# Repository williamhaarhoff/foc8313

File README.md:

# foc8313
This board was inspired by [Foc-Ctrl-Lite](https://github.com/peng-zhihui/Ctrl-FOC-Lite). FOC8313 is a highly compact, feature rich, daisy-chainable,  field oriented control board based around the DRV8313 3 phase half bridge driver. This board is highly configurable and upgradeable, and includes all the manufacturing files required start producing controllers for $\approx$ $20/board
|Front|Back|
|--| --|
| | |

## Features:
 - Highly compact 35x35mm outline
 - 29x29 square M3 hole pattern
 - 12V to 35V operating range
 - 3.5A max per phase current
 - Onboard STM32F103CBTx microcontroller
 - Based on the DRV8313 3 phase half bridge driver
 - 2 x INA240A2D high side current sense amplifiers
 - 1 x AS5047D back mounted hall effect encoder
 - EEPROM to store configurations / calibrations etc. 
 - Daisy chainable power and CAN
 - Programmable with USB-DFU or StLink - 6 pin tag connect
 - Auxilliary encoder/Timer port with 5V and GND
 - Auxilliary SPI/GPIO and I2C/UART port with 5V and GND
 - Easily upgradable for isolated CAN (3 wire)
 - Extremely compact isolated CAN
 - JLC manufacturing files included
 - Cost optimised for PCBA with JLCPCB (as few extended components as possible)
 - Most basic variant costs $\approx$ $20 per board (for 10 PCBs at JLCPCB)
 - Predominantly single sided design allows for cost effective single sided PCBA, easy hot plating for rework, easy configuration with jumpers

| Top | In1 |
|--| --|
|||
|In2 | Bottom|
|||

# PCBA - Cost Scaling:
| Version | Colour | Finish | Assembly      | Quantity | Unit price | Extended Price |
| -----   | ----   | ------ | -----         | -----    | ----       | ------         |
| v1.0    | Black  | Enig   | Standard T&B  | 15       |$30.8       | $462.57        |
| v1.0    | Black  | Enig   | Standard Top  | 15       |$24.3       | $364.22        |
| v1.0    | Black  | HASL   | Standard Top  | 10       |$24.75      | $247.51        |
| v1.0    | Black  | Enig   | Standard T&B  | 100      |$16.78      | $1678.39       |
| v1.0    | Green  | HASL   | Economic Top  | 2        |$53.45      | $106.89        |
| v1.0    | Green  | HASL   | Economic Top  | 5        |$30.28      | $151.40        |
| v1.0    | Green  | HASL   | Economic Top  | 10       |$20.48      | $204.81        |
| v1.0    | Green  | HASL   | Economic Top  | 15       |$19.2       | $288.48        |
| v1.0    | Green  | HASL   | Economic Top  | 30       |$15.6       | $468.48        |
| v1.0    | Green  | HASL   | Standard Top  | 100      |$12.98      | $1297.77       |
| v1.0    | Black  | Enig   | No ICs Top    | 10       |$15.9 +     | $159.37        |
| v1.0    | Black  | Enig   | No ICs Top    | 15       |$12.9 +     | $193.44        |

# ICs:
15x @LCSC: 215.22 -> 14.33
10x @LCSC: 146.71 -> 14.6

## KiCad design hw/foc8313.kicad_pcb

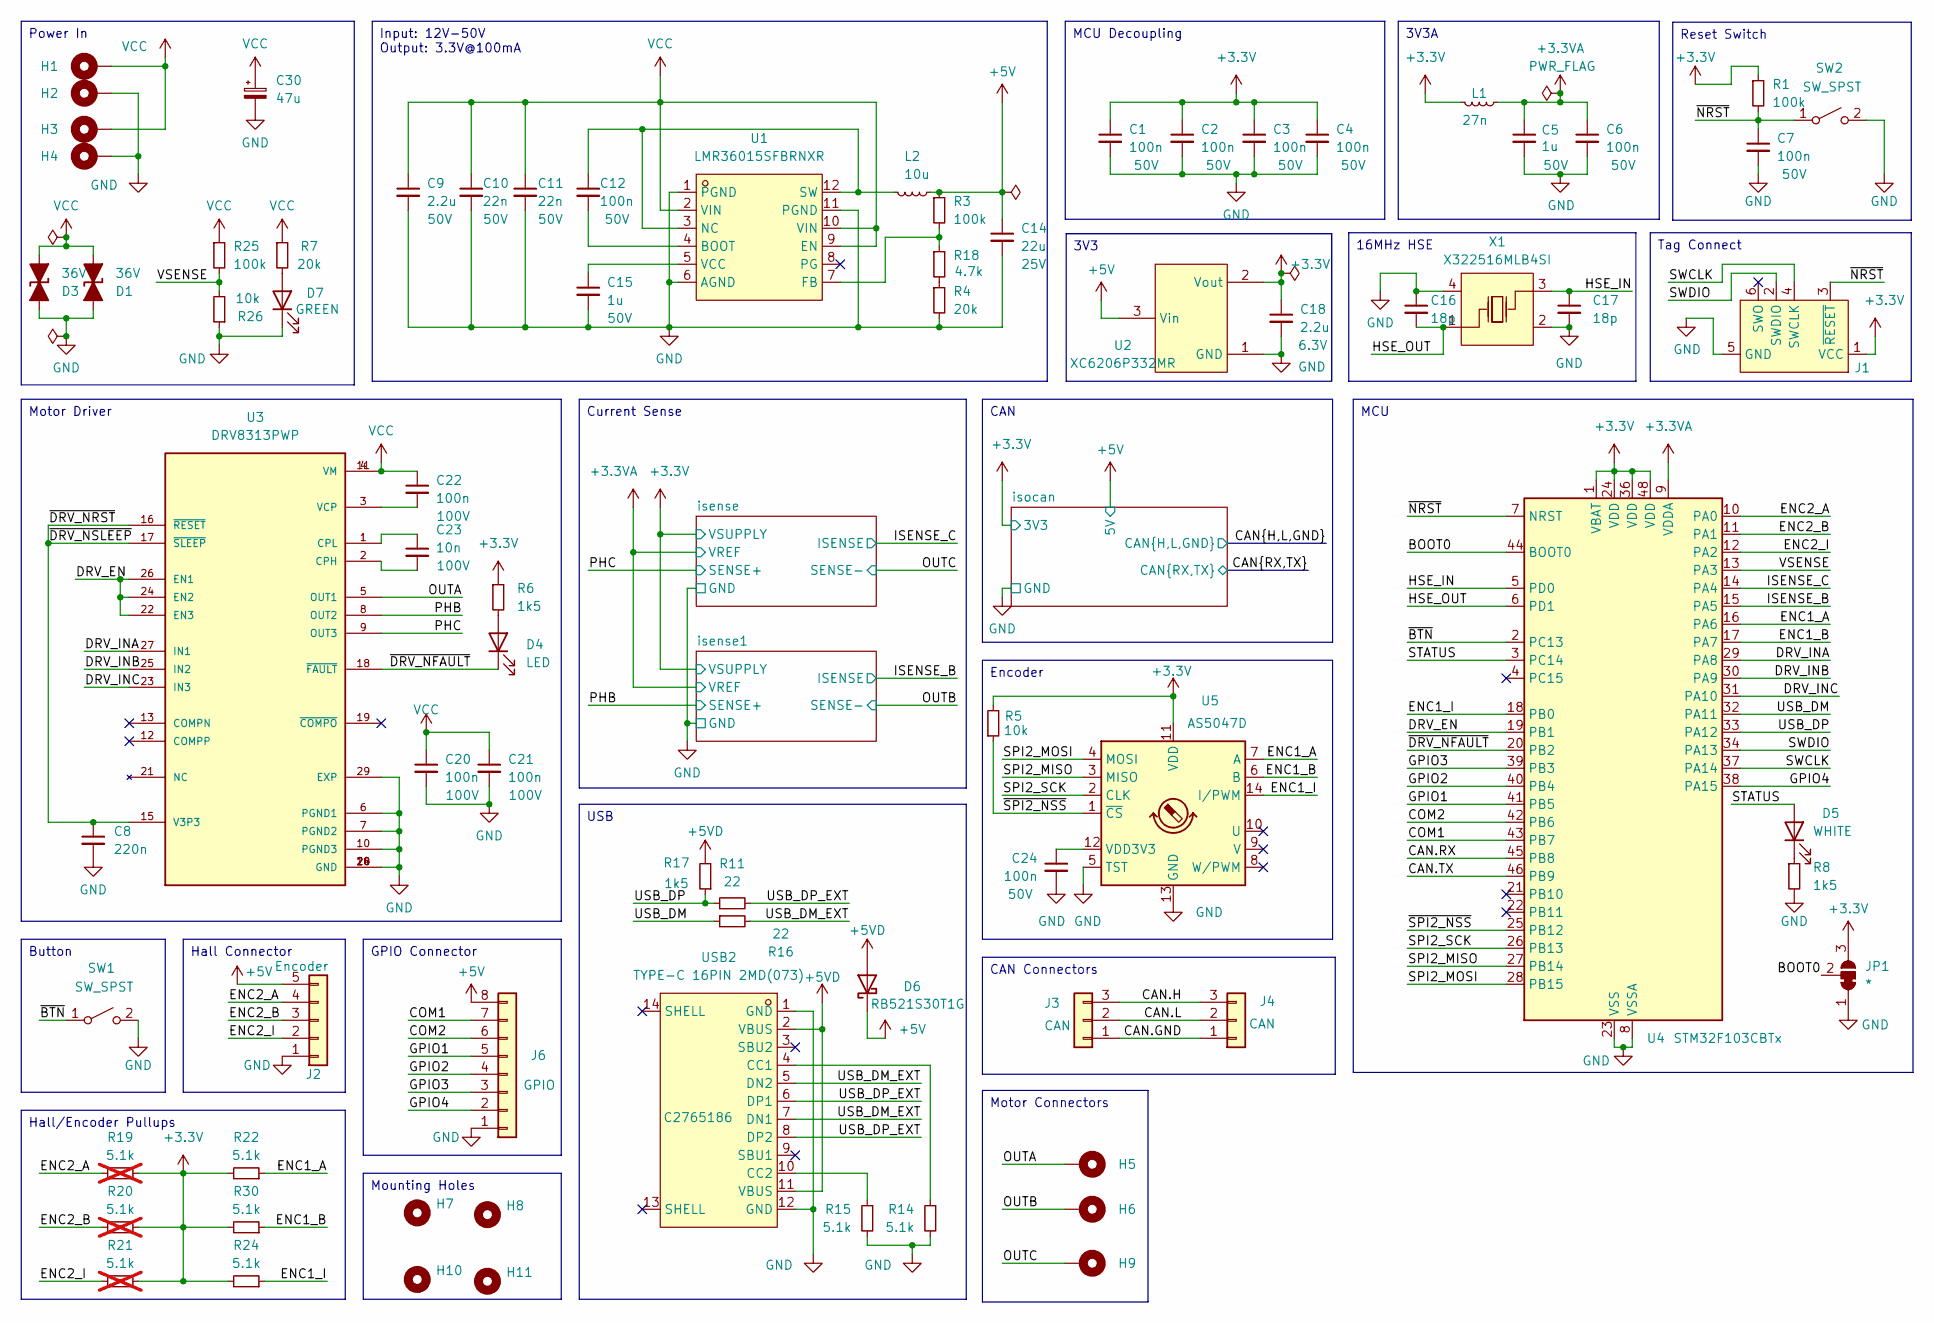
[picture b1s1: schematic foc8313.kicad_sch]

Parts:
C1, C2, C3, C4, C6, C7, C12, C24: 100n; C_0402_1005Metric; Rating 50V; LCSC C307331
C5, C15: 1u; C_0603_1608Metric; Rating 50V; LCSC C15849
C8: 220n; C_0402_1005Metric; LCSC C16772
C9: 2.2u; C_0805_2012Metric; Rating 50V; LCSC C377773
C10, C11: 22n; C_0402_1005Metric; Rating 50V; LCSC C1532
C14: 22u; C_0805_2012Metric; Rating 25V; LCSC C45783
C16, C17: 18p; C_0402_1005Metric; LCSC Part C1549
C18: 2.2u; C_0402_1005Metric; Rating 6.3V; LCSC C12530
C20, C21, C22: 100n; C_0402_1005Metric; Rating 100V; LCSC C307331
C23: 10n; C_0402_1005Metric; Rating 100V; LCSC C15195
C30: 47u; CP_Elec_5x5.7; LCSC C7471868
D1, D3: 36V; D_SOD-323; LCSC C92677
D4: LED; D_0603_1608Metric; LCSC C2286
D5: WHITE; LED_0603_1608Metric; LCSC C2290
D6: RB521S30T1G; D_SOD-523; LCSC C145179
D7: GREEN; LED_0603_1608Metric; LCSC C12624
H1, H2, H3, H4: MountingHole_Pad; 2x4
H5, H6, H9: MountingHole_Pad; 2x3
H7, H8, H10, H11: MountingHole; MountingHole_3.2mm_M3_DIN965_Pad_TopOnly
J1: Tag Connect; Tag-Connect_TC2030-IDC-NL_2x03_P1.27mm_Vertical
J2: Encoder; CONN-SMD_5P-P1.00_MEGASTAR_ZX-SH1.0-5PWT; LCSC Part C7430447
J3, J4: CAN; CONN-SMD_AFC10-S03QCA-00; LCSC Part C2764182
J6: GPIO; CONN-SMD_8P-P1.00_MEGASTAR_ZX-SH1.0-8PWT; LCSC Part C7430450
JP1: *; SolderJumper-3_P1.3mm_Bridged2Bar12_Pad1.0x1.5mm
L1: 27n; L_0603_1608Metric; LCSC C280267
L2: 10u; L_0805_2012Metric; LCSC C285963
R1, R3, R25: 100k; R_0402_1005Metric; LCSC C25741
R4, R7: 20k; R_0402_1005Metric; LCSC C25765
R5, R26: 10k; R_0402_1005Metric; LCSC C25744
R6, R8, R17: 1k5; R_0402_1005Metric; LCSC C25867
R11, R16: 22; R_0402_1005Metric; LCSC C25092
R14, R15, R22, R24, R30: 5.1k; R_0402_1005Metric; LCSC C25905
R18: 4.7k; R_0402_1005Metric; LCSC C25900
R19, R20, R21: 5.1k; R_0402_1005Metric; LCSC C25905; not fitted
SW1, SW2: SW_SPST; SW-TH_PANASONIC_EVPAKE31A; LCSC C569760
U1: LMR36015SFBRNXR; VQFN-12_L3.0-W2.0-P0.65-BL_TI_RNX; LCSC Part C3187929
U2: XC6206P332MR; SOT-23-3_L2.9-W1.6-P1.90-LS2.8-BR; LCSC Part C5446
U3: DRV8313PWP; HTSSOP-28_L9.8-W4.5-P0.65-LS6.6-BL-EP; PARTREV D; LCSC C92482
U4: STM32F103CBTx; LQFP-48_7x7mm_P0.5mm; LCSC C8304
U5: AS5047D; TSSOP-14_4.4x5mm_P0.65mm; LCSC C962063
USB2: TYPE-C 16PIN 2MD(073); USB-C-SMD_TYPE-C-6PIN-2MD-073; LCSC Part C2765186
X1: X322516MLB4SI; OSC-SMD_4P-L3.2-W2.5-BL; LCSC Part C13738

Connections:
+3.3V: C1.1, C2.1, C3.1, C4.1, C18.1, J1.1 (VCC), JP1.3 (B), L1.2, R1.1, R5.2, R6.1, R19.2, R20.2, R21.2, R22.2, R24.2, R30.2, U2.2 (Vout), U4.1 (VBAT), U4.24 (VDD), U4.36 (VDD), U4.48 (VDD), U5.11 (VDD); also elsewhere on the board
+3.3VA: C5.1, C6.1, L1.1, U4.9 (VDDA); also elsewhere on the board
+5V: C14.1, D6.1 (K), J2.5, J6.8, L2.1, R3.1, U2.3 (Vin); also elsewhere on the board
+5VD: D6.2 (A), R17.2, USB2.2 (VBUS), USB2.11 (VBUS)
/BOOT0: JP1.2 (C), U4.44 (BOOT0)
/CAN.GND: J3.1, J4.1; also elsewhere on the board
/CAN.H: J3.3, J4.3; also elsewhere on the board
/CAN.L: J3.2, J4.2; also elsewhere on the board
/CAN.RX: U4.45 (PB8); also elsewhere on the board
/CAN.TX: U4.46 (PB9); also elsewhere on the board
/COM1: J6.7, U4.43 (PB7)
/COM2: J6.6, U4.42 (PB6)
/DRV_EN: U3.22 (EN3), U3.24 (EN2), U3.26 (EN1), U4.19 (PB1)
/DRV_INA: U3.27 (IN1), U4.29 (PA8)
/DRV_INB: U3.25 (IN2), U4.30 (PA9)
/DRV_INC: U3.23 (IN3), U4.31 (PA10)
/ENC1_A: R22.1, U4.16 (PA6), U5.7 (A)
/ENC1_B: R30.1, U4.17 (PA7), U5.6 (B)
/ENC1_I: R24.1, U4.18 (PB0), U5.14 (I/PWM)
/ENC2_A: J2.4, R19.1, U4.10 (PA0)
/ENC2_B: J2.3, R20.1, U4.11 (PA1)
/ENC2_I: J2.2, R21.1, U4.12 (PA2)
/GPIO1: J6.5, U4.41 (PB5)
/GPIO2: J6.4, U4.40 (PB4)
/GPIO3: J6.3, U4.39 (PB3)
/GPIO4: J6.2, U4.38 (PA15)
/HSE_IN: C17.1, U4.5 (PD0), X1.3
/HSE_OUT: C16.2, U4.6 (PD1), X1.1
/ISENSE_B: U4.15 (PA5); also elsewhere on the board
/ISENSE_C: U4.14 (PA4); also elsewhere on the board
/OUTA: H5.1, U3.5 (OUT1)
/OUTB: H6.1; also elsewhere on the board
/OUTC: H9.1; also elsewhere on the board
/PHB: U3.8 (OUT2); also elsewhere on the board
/PHC: U3.9 (OUT3); also elsewhere on the board
/SPI2_MISO: U4.27 (PB14), U5.3 (MISO)
/SPI2_MOSI: U4.28 (PB15), U5.4 (MOSI)
/SPI2_SCK: U4.26 (PB13), U5.2 (CLK)
/STATUS: D5.2 (A), U4.3 (PC14)
/SWCLK: J1.4 (SWCLK), U4.37 (PA14)
/SWDIO: J1.2 (SWDIO), U4.34 (PA13)
/USB_DM: R16.1, U4.32 (PA11)
/USB_DM_EXT: R16.2, USB2.5 (DN2), USB2.7 (DN1)
/USB_DP: R11.1, R17.1, U4.33 (PA12)
/USB_DP_EXT: R11.2, USB2.6 (DP1), USB2.8 (DP2)
/VSENSE: R25.2, R26.2, U4.13 (PA3)
/~BTN: SW1.1 (A), U4.2 (PC13)
/~DRV_NFAULT: D4.1 (K), U3.18 (~FAULT), U4.20 (PB2)
/~DRV_NRST: C8.1, U3.15 (V3P3), U3.16 (~RESET), U3.17 (~SLEEP)
/~NRST: C7.1, J1.3 (~RESET), R1.2, SW2.1 (A), U4.7 (NRST)
/~SPI2_NSS: R5.1, U4.25 (PB12), U5.1 (~CS)
GND: C1.2, C2.2, C3.2, C4.2, C5.2, C6.2, C7.2, C8.2, C9.2, C10.2, C11.2, C14.2, C15.2, C16.1, C17.2, C18.2, C20.2, C21.2, C24.2, C30.2, D1.2 (A2), D3.2 (A2), D7.1 (K), H2.1, H4.1, J1.5 (GND), J2.1, J6.1, JP1.1 (A), R4.2, R8.2, R14.2, R15.2, R26.1, SW1.2 (B), SW2.2 (B), U1.1 (PGND), U1.6 (AGND), U1.11 (PGND), U2.1 (GND), U3.6 (PGND1), U3.7 (PGND2), U3.10 (PGND3), U3.14 (GND), U3.20 (GND), U3.28 (GND), U3.29 (EXP), U4.8 (VSSA), U4.23 (VSS), U4.35 (VSS), U4.47 (VSS), U5.5 (TST), U5.13 (GND), USB2.1 (GND), USB2.12 (GND), X1.2, X1.4; also elsewhere on the board
unnamed: D4.2 (A), R6.2
unnamed: D5.1 (K), R8.1
unnamed: D7.2 (A), R7.2
unnamed: R4.1, R18.2
unnamed: C12.2, U1.4 (BOOT)
unnamed: R3.2, R18.1, U1.7 (FB)
unnamed: C12.1, L2.2, U1.3 (NC), U1.12 (SW)
unnamed: C15.1, U1.5 (VCC)
unnamed: C23.2, U3.2 (CPH)
unnamed: C23.1, U3.1 (CPL)
unnamed: C22.2, U3.3 (VCP)
unnamed: C24.1, U5.12 (VDD3V3)
unnamed: R14.1, USB2.4 (CC1)
unnamed: R15.1, USB2.10 (CC2)
VCC: C9.1, C10.1, C11.1, C20.1, C21.1, C22.1, C30.1, D1.1 (A1), D3.1 (A1), H1.1, H3.1, R7.1, R25.1, U1.2 (VIN), U1.9 (EN), U1.10 (VIN), U3.4 (VM), U3.11 (VM)

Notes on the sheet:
Motor Connectors
Mounting Holes
MCU
CAN Connectors
GPIO Connector
Reset Switch
3V3A
16MHz HSE
3V3
MCU Decoupling
CAN
Hall/Encoder Pullups
Hall Connector
Power In
Encoder
Tag Connect
Current Sense
Button
Motor Driver
USB
Input: 12V-50V Output: 3.3V@100mA

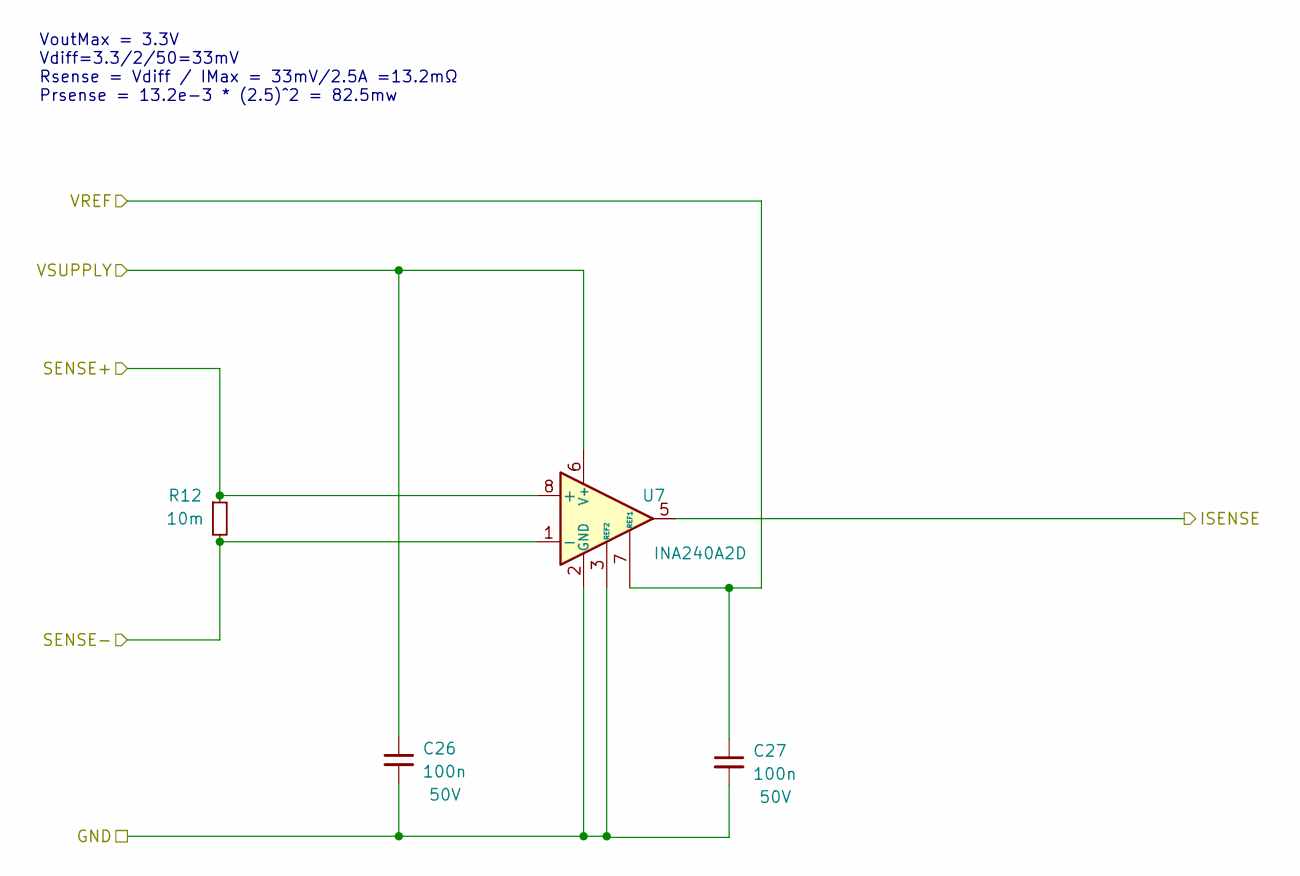
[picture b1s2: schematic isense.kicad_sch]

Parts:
C26, C27: 100n; C_0402_1005Metric; Rating 50V; LCSC C307331
R12: 10m; R_0805_2012Metric; LCSC C601083
U7: INA240A2D; SOIC-8_3.9x4.9mm_P1.27mm; LCSC C2060768

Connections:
+3.3V: C26.1, U7.6 (V+); also elsewhere on the board
+3.3VA: C27.1, U7.7 (REF1); also elsewhere on the board
/ISENSE_C: U7.5; also elsewhere on the board
/OUTC: R12.2, U7.1 (-); also elsewhere on the board
/PHC: R12.1, U7.8 (+); also elsewhere on the board
GND: C26.2, C27.2, U7.2 (GND), U7.3 (REF2), U7.4 (GND); also elsewhere on the board

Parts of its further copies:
C28, C29: 100n; C_0402_1005Metric; Rating 50V; LCSC C307331
R13: 10m; R_0805_2012Metric; LCSC C601083
U8: INA240A2D; SOIC-8_3.9x4.9mm_P1.27mm; LCSC C2060768

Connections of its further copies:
+3.3V: C28.1, U8.6 (V+); also elsewhere on the board
+3.3VA: C29.1, U8.7 (REF1); also elsewhere on the board
/ISENSE_B: U8.5; also elsewhere on the board
/OUTB: R13.2, U8.1 (-); also elsewhere on the board
/PHB: R13.1, U8.8 (+); also elsewhere on the board
GND: C28.2, C29.2, U8.2 (GND), U8.3 (REF2), U8.4 (GND); also elsewhere on the board

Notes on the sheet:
VoutMax = 3.3V Vdiff=3.3/2/50=33mV Rsense = Vdiff / IMax = 33mV/2.5A =13.2mΩ Prsense = 13.2e-3 * (2.5)^2 = 82.5mw

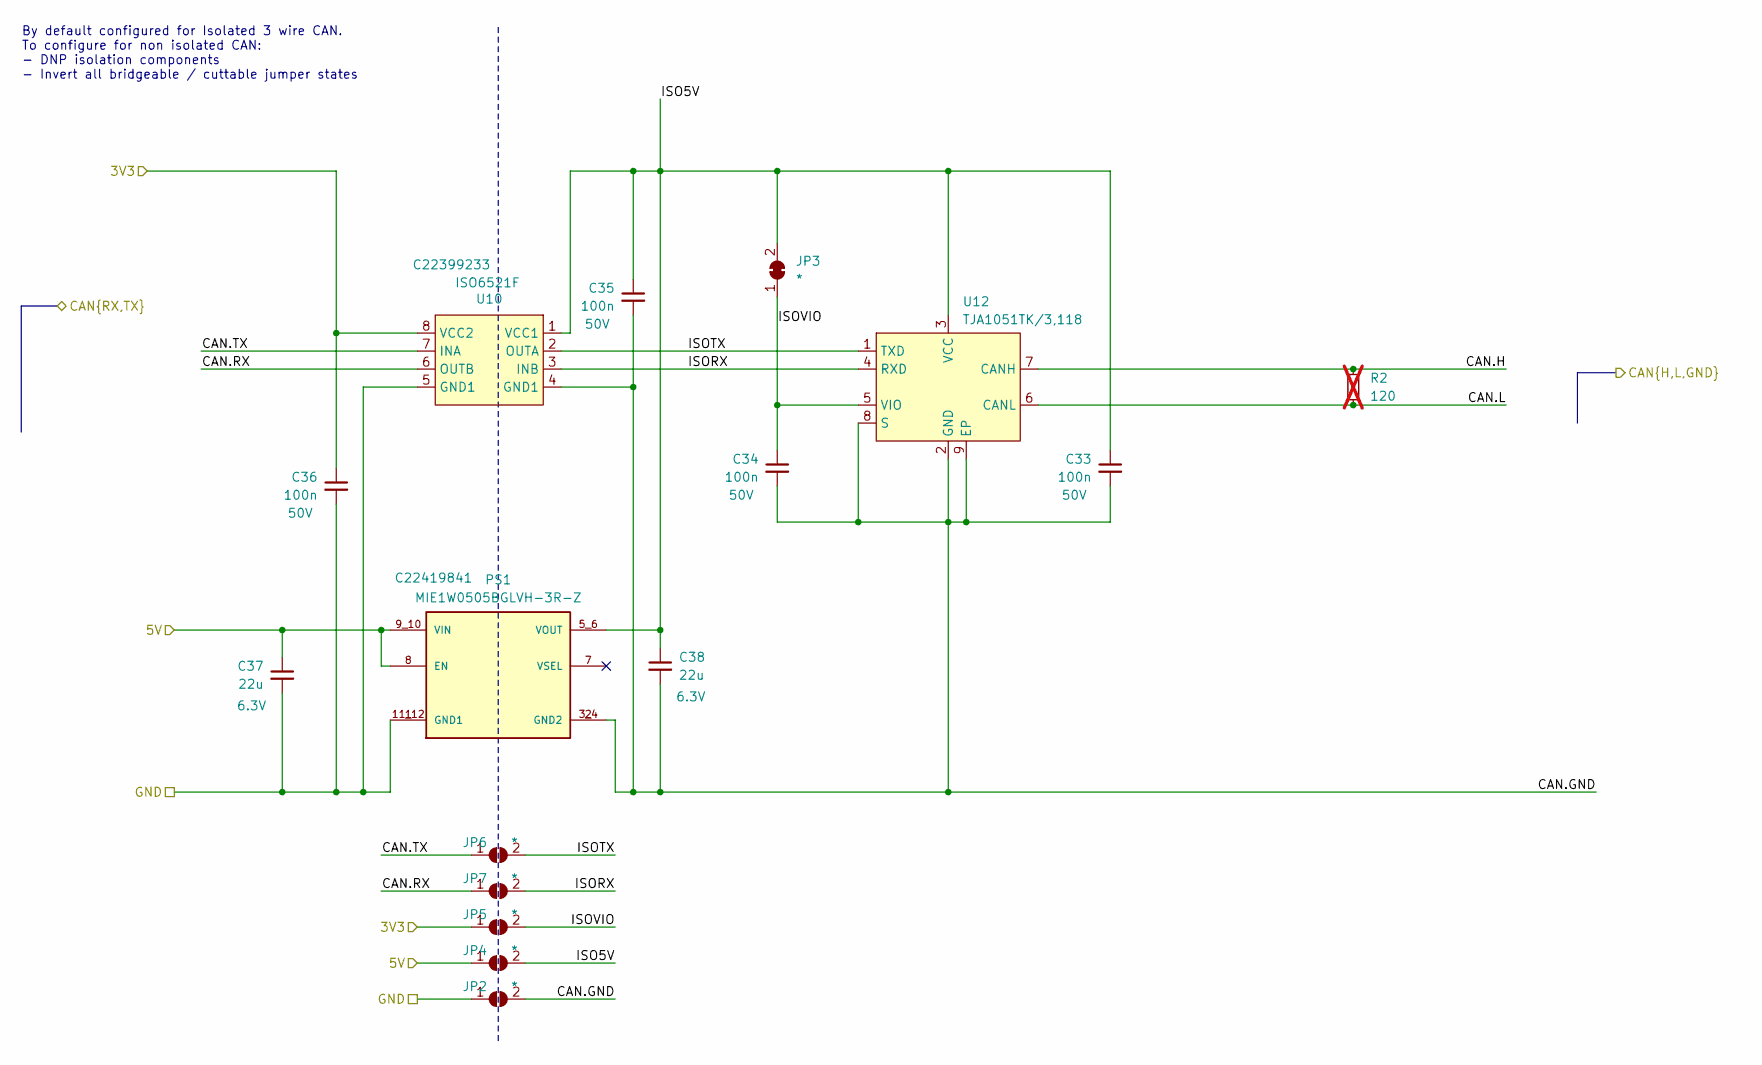
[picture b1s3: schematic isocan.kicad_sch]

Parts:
C33, C34, C35, C36: 100n; C_0402_1005Metric; Rating 50V; LCSC C307331
C37, C38: 22u; C_0603_1608Metric; Rating 6.3V; LCSC C59461
JP2, JP4, JP5, JP6, JP7: *; jumper12_open
JP3: *; jumper12_closed
PS1: MIE1W0505BGLVH-3R-Z; CONV_MIE1W0505BGLVH-3R-Z; PARTREV 0.8; LCSC C22419841
R2: 120; R_0603_1608Metric; LCSC C22787; not fitted
U10: ISO6521F; DFN-8-1EP_3x2mm_P0.5mm_EP1.3x1.5mm; LCSC C22399233
U12: TJA1051TK/3,118; HVSON-8_L3.0-W3.0-P0.65-BL-EP; LCSC Part C124020

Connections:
+3.3V: C36.1, JP5.1 (A), U10.8 (VCC2); also elsewhere on the board
+5V: C37.1, JP4.1 (A), PS1.8 (EN), PS1.9_10 (VIN); also elsewhere on the board
/CAN.GND: C33.2, C34.2, C35.2, C38.2, JP2.2 (B), PS1.2 (GND2), PS1.3_4 (GND2), U10.4 (GND1), U12.2 (GND), U12.8 (S), U12.9 (EP); also elsewhere on the board
/CAN.H: R2.1, U12.7 (CANH); also elsewhere on the board
/CAN.L: R2.2, U12.6 (CANL); also elsewhere on the board
/CAN.RX: JP7.1 (A), U10.6 (OUTB); also elsewhere on the board
/CAN.TX: JP6.1 (A), U10.7 (INA); also elsewhere on the board
/isocan/ISO5V: C33.1, C35.1, C38.1, JP3.2 (B), JP4.2 (B), PS1.5_6 (VOUT), U10.1 (VCC1), U12.3 (VCC)
/isocan/ISORX: JP7.2 (B), U10.3 (INB), U12.4 (RXD)
/isocan/ISOTX: JP6.2 (B), U10.2 (OUTA), U12.1 (TXD)
/isocan/ISOVIO: C34.1, JP3.1 (A), JP5.2 (B), U12.5 (VIO)
GND: C36.2, C37.2, JP2.1 (A), PS1.1 (GND1), PS1.11_12 (GND1), U10.5 (GND1); also elsewhere on the board

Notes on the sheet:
By default configured for Isolated 3 wire CAN. To configure for non isolated CAN: - DNP isolation components - Invert all bridgeable / cuttable jumper states

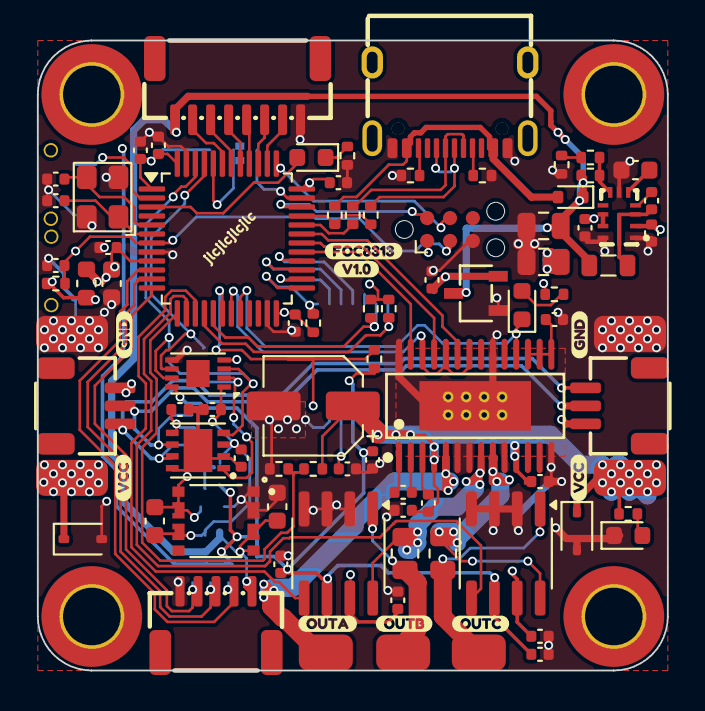
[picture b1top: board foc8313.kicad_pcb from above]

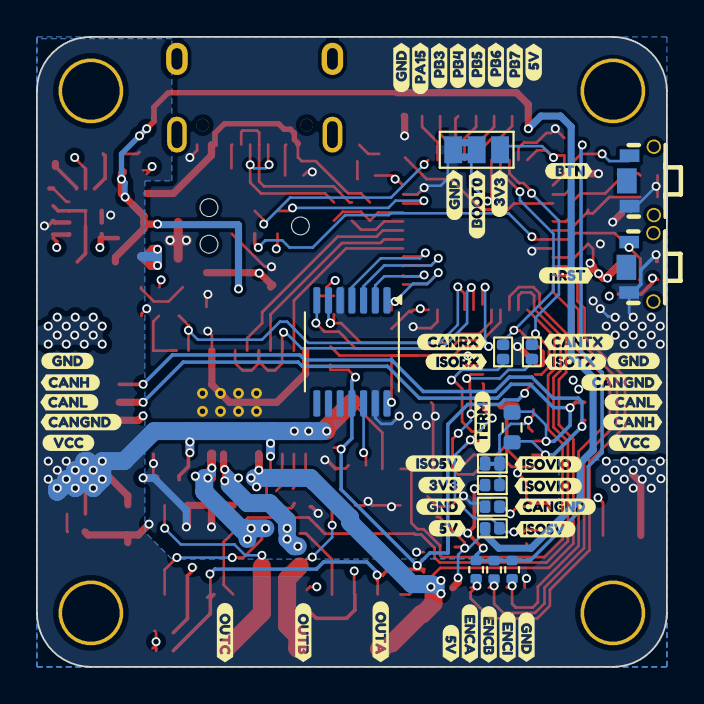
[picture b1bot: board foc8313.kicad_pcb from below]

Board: 4 copper layers, 35.0 x 35.0 mm, 155 parts (58 on the bottom side), 71 nets.

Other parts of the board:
kibuzzard-690CC9D7: G***; kibuzzard-690CC9D7
kibuzzard-690CC938: G***; kibuzzard-690CC938
kibuzzard-6687B96D: G***; kibuzzard-6687B96D
kibuzzard-6687B97C: G***; kibuzzard-6687B97C
kibuzzard-6687B916, kibuzzard-6687B916#2, kibuzzard-6687B916#3, kibuzzard-6687B916#4: G***; kibuzzard-6687B916
kibuzzard-6687B962: G***; kibuzzard-6687B962
kibuzzard-6687B975: G***; kibuzzard-6687B975
kibuzzard-6687B983: G***; kibuzzard-6687B983
kibuzzard-6687B989: G***; kibuzzard-6687B989
kibuzzard-6687B990, kibuzzard-6687B990#2: G***; kibuzzard-6687B990
kibuzzard-6687BB13: G***; kibuzzard-6687BB13
kibuzzard-6687BB22: G***; kibuzzard-6687BB22
kibuzzard-6687BB56: G***; kibuzzard-6687BB56
kibuzzard-6687BB64: G***; kibuzzard-6687BB64
kibuzzard-6687BBB1: G***; kibuzzard-6687BBB1
kibuzzard-6687BBBA: G***; kibuzzard-6687BBBA
kibuzzard-6687BBC5: G***; kibuzzard-6687BBC5
kibuzzard-6687BC5B: G***; kibuzzard-6687BC5B
kibuzzard-6687BC6D: G***; kibuzzard-6687BC6D
kibuzzard-6687BC64: G***; kibuzzard-6687BC64
kibuzzard-6687BCF3, kibuzzard-6687BCF3#2: G***; kibuzzard-6687BCF3
kibuzzard-6687BD2B, kibuzzard-6687BD2B#2: G***; kibuzzard-6687BD2B
kibuzzard-6687BD8E, kibuzzard-6687BD8E#2: G***; kibuzzard-6687BD8E
kibuzzard-6687BD9D: G***; kibuzzard-6687BD9D
kibuzzard-6687BD69: G***; kibuzzard-6687BD69
kibuzzard-6687BD70: G***; kibuzzard-6687BD70
kibuzzard-6687BD76: G***; kibuzzard-6687BD76
kibuzzard-6687BD97: G***; kibuzzard-6687BD97
kibuzzard-6687BF5D: G***; kibuzzard-6687BF5D
kibuzzard-6687BF56: G***; kibuzzard-6687BF56
kibuzzard-6687BFAE: G***; kibuzzard-6687BFAE
kibuzzard-6687BFB6: G***; kibuzzard-6687BFB6
kibuzzard-6687BFD2: G***; kibuzzard-6687BFD2
kibuzzard-6687BFE6: G***; kibuzzard-6687BFE6
kibuzzard-6687C00C, kibuzzard-6687C00C#2: G***; kibuzzard-6687C00C
kibuzzard-6687C0E6: G***; kibuzzard-6687C0E6
kibuzzard-6687C3AC, kibuzzard-6687C3AC#2: G***; kibuzzard-6687C3AC
kibuzzard-6687C12A: G***; kibuzzard-6687C12A
kibuzzard-6687C148: G***; kibuzzard-6687C148
kibuzzard-6687C371, kibuzzard-6687C371#2: G***; kibuzzard-6687C371
kibuzzard-6687C408: G***; kibuzzard-6687C408
kibuzzard-6687C440: G***; kibuzzard-6687C440
kibuzzard-6687C487: G***; kibuzzard-6687C487

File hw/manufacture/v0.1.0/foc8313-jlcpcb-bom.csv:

"Comment","Designator","Footprint","LCSC Part Number"
"100n","C1,C2,C3,C4,C6,C7,C12,C20,C21,C22,C24,C25,C26,C27,C28,C29,C33,C34,C35,C36","C_0402_1005Metric","C307331"
"1u","C5,C15","C_0603_1608Metric","C15849"
"220n","C8","C_0402_1005Metric","C16772"
"2.2u","C9","C_0805_2012Metric","C377773"
"22n","C10,C11","C_0402_1005Metric","C1532"
"4.7p","C13","C_0402_1005Metric","C1567"
"22u","C14","C_0805_2012Metric","C45783"
"18p","C16,C17","C_0402_1005Metric","C1549"
"2.2u","C18","C_0402_1005Metric","C12530"
"10n","C23","C_0402_1005Metric","C15195"
"47u","C30","CP_Elec_5x5.7","C7471868"
"22u","C37,C38","C_0603_1608Metric","C59461"
"36V","D1,D3","D_SOD-323","C92677"
"RB521S30T1G","D2,D6","D_SOD-523","C145179"
"LED","D4","D_0603_1608Metric","C2286"
"WHITE","D5","LED_0603_1608Metric","C2290"
"YELLOW","D7","LED_0603_1608Metric","C72038"
"MountingHole_Pad","H1,H2,H3,H4","2x4","no_part_number"
"MountingHole_Pad","H5,H6,H9","2x3","no_part_number"
"MountingHole","H7,H8,H10,H11","MountingHole_3.2mm_M3_DIN965_Pad_TopOnly","no_part_number"
"Tag Connect","J1","Tag-Connect_TC2030-IDC-NL_2x03_P1.27mm_Vertical","no_part_number"
"Encoder","J2","CONN-SMD_5P-P1.00_MEGASTAR_ZX-SH1.0-5PWT","C7430447"
"CAN","J3,J4","CONN-SMD_AFC10-S03QCA-00","C2764182"
"GPIO","J6","CONN-SMD_8P-P1.00_MEGASTAR_ZX-SH1.0-8PWT","C7430450"
"*","JP1","SolderJumper-3_P1.3mm_Bridged2Bar12_Pad1.0x1.5mm","no_part_number"
"*","JP2,JP4,JP5,JP6,JP7","jumper12_open","no_part_number"
"*","JP3","jumper12_closed","no_part_number"
"27n","L1","L_0603_1608Metric","C280267"
"10u","L2","L_0805_2012Metric","C285963"
"MIE1W0505BGLVH-3R-Z","PS1","CONV_MIE1W0505BGLVH-3R-Z","no_part_number"
"100k","R1,R3","R_0402_1005Metric","C25741"
"120","R2","R_0603_1608Metric","C22787"
"20k","R4,R7","R_0402_1005Metric","C25765"
"10k","R5,R9,R10","R_0402_1005Metric","C25744"
"1k5","R6,R8,R17","R_0402_1005Metric","C25867"
"22","R11,R16","R_0402_1005Metric","C25092"
"6m","R12,R13","R_0805_2012Metric","C728268"
"5.1k","R14,R15","R_0402_1005Metric","C25905"
"4.7k","R18","R_0402_1005Metric","C25900"
"SW_SPST","SW1,SW2","SW-TH_PANASONIC_EVPAKE31A","C569760"
"LMR36015SFBRNXR","U1","VQFN-12_L3.0-W2.0-P0.65-BL_TI_RNX","C3187929"
"XC6206P332MR","U2","SOT-23-3_L2.9-W1.6-P1.90-LS2.8-BR","C5446"
"DRV8313PWP","U3","HTSSOP-28_L9.8-W4.5-P0.65-LS6.6-BL-EP","C92482"
"STM32F103CBTx","U4","LQFP-48_7x7mm_P0.5mm","C8304"
"AS5047D","U5","TSSOP-14_4.4x5mm_P0.65mm","C962063"
"ZD24C08AE1-STGMT","U6","SOT-23-5_L3.0-W1.7-P0.95-LS2.8-BL","C3007877"
"INA240A2D","U7,U8","SOIC-8_3.9x4.9mm_P1.27mm","C2060768"
"ISO6521F","U10","DFN-8-1EP_3x2mm_P0.5mm_EP1.3x1.5mm","no_part_number"
"TJA1051TK/3,118","U12","HVSON-8_L3.0-W3.0-P0.65-BL-EP","C124020"
"USB3.1-TYPE-C-FSABC","USB1","USB-3.1-SMD_USB3.1-TYPE-C-FSABC","C319140"
"X322516MLB4SI","X1","OSC-SMD_4P-L3.2-W2.5-BL","C13738"

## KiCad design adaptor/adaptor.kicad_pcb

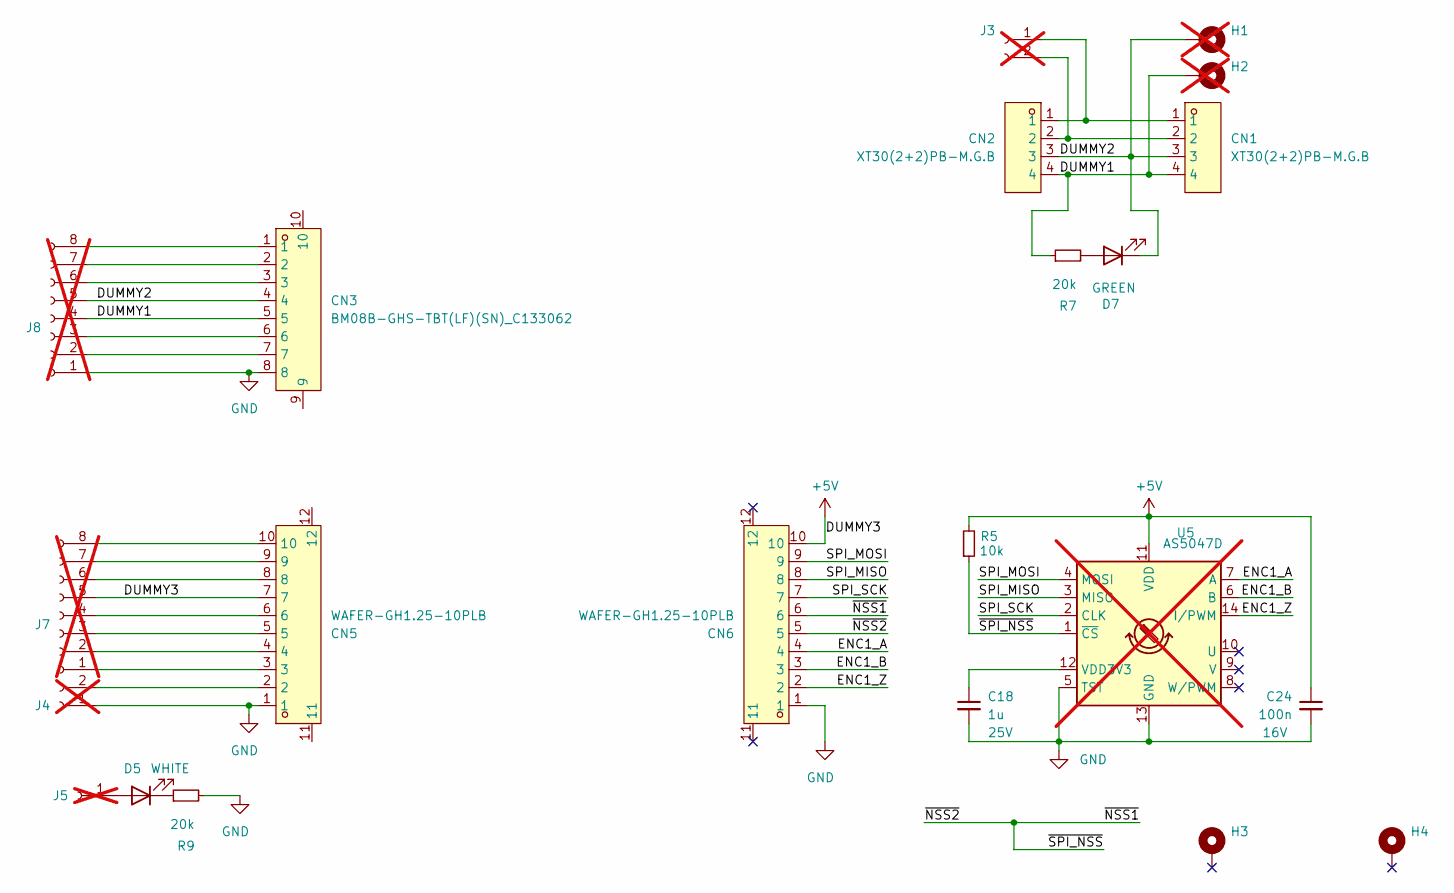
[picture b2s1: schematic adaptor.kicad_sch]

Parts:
C18: 1u; C_0402_1005Metric; Rating 25V; LCSC C52923
C24: 100n; C_0402_1005Metric; Rating 16V; LCSC C1525
CN1, CN2: XT30(2+2)PB-M.G.B; CONN-TH_XT30PB-M; LCSC Part C19268029
CN3: BM08B-GHS-TBT(LF)(SN)_C133062; CONN-SMD_BM08B-GHS-TBT-LF-SN; LCSC Part C133062
CN5, CN6: WAFER-GH1.25-10PLB; CONN-SMD_10P-P1.25_XUNPU_WAFER-GH1.25-10PLB; LCSC Part C3029376
D5: WHITE; LED_0603_1608Metric; LCSC C2290
D7: GREEN; LED_0603_1608Metric; LCSC C2297
H1, H2: TestPoint_Keystone_5005-5009_Compact; not fitted
H3, H4: MountingHole_Pad; MountingHole_3.2mm_M3_ISO7380_Pad_TopBottom
J3: PinHeader_1x02_P2.00mm_Vertical; not fitted
J4: Conn_01x02_Socket; PinHeader_1x02_P1.27mm_Vertical; not fitted
J5: Conn_01x02_Socket; PinHeader_1x01_P1.27mm_Vertical; not fitted
J7, J8: Conn_01x08_Socket; PinHeader_1x08_P1.27mm_Vertical; not fitted
R5: 10k; R_0402_1005Metric; LCSC C25744
R7, R9: 20k; R_0402_1005Metric; LCSC C25765
U5: AS5047D; TSSOP-14_4.4x5mm_P0.65mm; LCSC C962063; not fitted

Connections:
+5V: C24.1, CN5.7, CN6.10, J7.5, R5.2, U5.11 (VDD)
/DUMMY1: CN1.4, CN2.4, CN3.5, H2.1, J8.4, R7.1
/DUMMY2: CN1.3, CN2.3, CN3.4, D7.1 (K), H1.1, J8.5
/ENC1_A: CN6.4, U5.7 (A)
/ENC1_B: CN6.3, U5.6 (B)
/ENC1_Z: CN6.2, U5.14 (I/PWM)
/SPI_MISO: CN6.8, U5.3 (MISO)
/SPI_MOSI: CN6.9, U5.4 (MOSI)
/SPI_SCK: CN6.7, U5.2 (CLK)
/~NSS1: CN6.5, CN6.6, R5.1, U5.1 (~CS)
GND: C18.2, C24.2, CN3.8, CN5.1, CN6.1, J4.1, J8.1, R9.2, U5.5 (TST), U5.13 (GND)
unnamed: D5.2 (A), J5.1
unnamed: D5.1 (K), R9.1
unnamed: D7.2 (A), R7.2
unnamed: CN1.1, CN2.1, J3.1
unnamed: CN1.2, CN2.2, J3.2
unnamed: CN5.2, J4.2
unnamed: CN5.3, J7.1
unnamed: CN5.4, J7.2
unnamed: CN5.5, J7.3
unnamed: CN5.6, J7.4
unnamed: CN5.8, J7.6
unnamed: CN5.9, J7.7
unnamed: CN5.10, J7.8
unnamed: CN3.7, J8.2
unnamed: CN3.6, J8.3
unnamed: CN3.3, J8.6
unnamed: CN3.2, J8.7
unnamed: CN3.1, J8.8
unnamed: C18.1, U5.12 (VDD3V3)

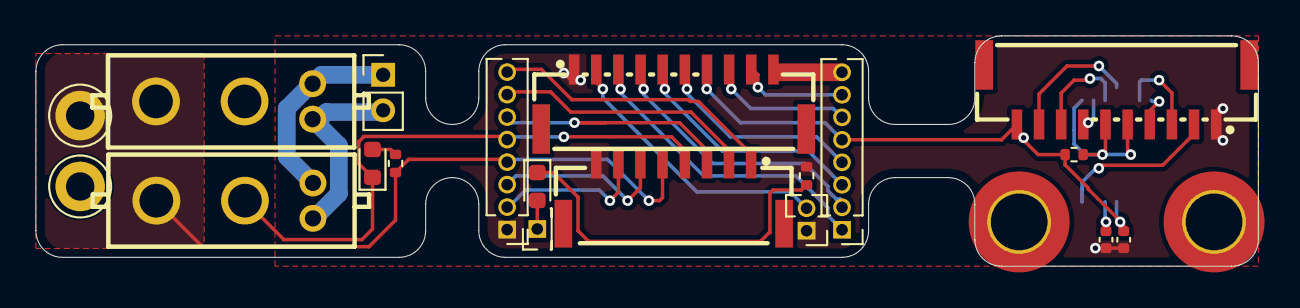
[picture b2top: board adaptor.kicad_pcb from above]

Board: 2 copper layers, 69.0 x 13.0 mm, 22 parts (1 on the bottom side), 30 nets.

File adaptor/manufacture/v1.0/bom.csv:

Designator,Footprint,Quantity,Value,LCSC Part #
C18,0402,1,1u,C52923
C24,0402,1,100n,C1525
"CN1, CN2",CONN-TH_XT30PB-M,2,XT30(2+2)PB-M.G.B,C19268029
CN3,CONN-SMD_BM08B-GHS-TBT-LF-SN,1,BM08B-GHS-TBT(LF)(SN)_C133062,C133062
"CN5, CN6",CONN-SMD_10P-P1.25_XUNPU_WAFER-GH1.25-10PLB,2,WAFER-GH1.25-10PLB,C3029376
D5,0603,1,WHITE,C2290
D7,0603,1,GREEN,C2297
J3,PinHeader_1x02_P2.00mm_Vertical,1,~,
J4,PinHeader_1x02_P1.27mm_Vertical,1,Conn_01x02_Socket,
J5,PinHeader_1x01_P1.27mm_Vertical,1,Conn_01x02_Socket,
"J7, J8",PinHeader_1x08_P1.27mm_Vertical,2,Conn_01x08_Socket,
R5,0402,1,10k,C25744
"R7, R9",0402,2,20k,C25765
U5,TSSOP-14_4.4x5mm_P0.65mm,1,AS5047D,C962063

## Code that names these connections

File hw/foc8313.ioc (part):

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Mcu.Name=STM32F103C(8-B)Tx
Mcu.Package=LQFP48
Mcu.UserName=STM32F103CBTx
PA0-WKUP.Signal=S_TIM2_CH1_ETR
PA1.Signal=S_TIM2_CH2
PA10.Signal=S_TIM1_CH3
PA11.Mode=Device
PA11.Signal=USB_DM
PA12.Mode=Device
PA12.Signal=USB_DP
PA13.Mode=Serial_Wire
PA13.Signal=SYS_JTMS-SWDIO
PA14.Mode=Serial_Wire
PA14.Signal=SYS_JTCK-SWCLK
PA15.Signal=GPIO_Output
PA2.Signal=S_TIM2_CH3
PA3.Signal=ADCx_IN3
PA4.Signal=ADCx_IN4
PA5.Signal=ADCx_IN5
PA6.Signal=S_TIM3_CH1
PA7.Signal=S_TIM3_CH2
PA8.Signal=S_TIM1_CH1
PA9.Signal=S_TIM1_CH2
PB0.Signal=S_TIM3_CH3
PB1.Signal=GPIO_Output
PB12.GPIOParameters=GPIO_Label
PB12.GPIO_Label=SPI2_NSS
PB12.Signal=GPIO_Output
PB13.Mode=Full_Duplex_Master
PB13.Signal=SPI2_SCK
PB14.Mode=Full_Duplex_Master
PB14.Signal=SPI2_MISO
PB15.Mode=Full_Duplex_Master
PB15.Signal=SPI2_MOSI
PB2.Signal=GPIO_Input
PB3.Mode=Full_Duplex_Master
PB3.Signal=SPI1_SCK
PB4.Mode=Full_Duplex_Master
PB4.Signal=SPI1_MISO
PB5.Mode=Full_Duplex_Master
PB5.Signal=SPI1_MOSI
PB6.Mode=Asynchronous
PB6.Signal=USART1_TX
PB7.Mode=Asynchronous
PB7.Signal=USART1_RX
PB8.Mode=CAN_Activate
PB8.Signal=CAN_RX
PB9.Mode=CAN_Activate
PB9.Signal=CAN_TX
PC13-TAMPER-RTC.Signal=GPIO_Input
PC14-OSC32_IN.Signal=GPIO_Output
PD0-OSC_IN.Mode=HSE-External-Oscillator
PD0-OSC_IN.Signal=RCC_OSC_IN
PD1-OSC_OUT.Mode=HSE-External-Oscillator
PD1-OSC_OUT.Signal=RCC_OSC_OUT
board=custom

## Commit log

2024-06-29 [hw] Setting up project, starting to layout schematic
2024-06-29 [Hw] compact discrete 4 wire iso can, approx drv routing, eeprom
2024-06-29 [Hw] 5V buck, Isocan, Encoder, MCU, with LCSC parts
2024-06-29 WIP XT30?
2024-06-29 [Hw] Rough incomplete layout and component placement
2024-06-29 [Hw] No iso can, 0402 where possible, approx layout and formfactor
2024-06-29 [Hw] Squeezing in push button and aux 8 pin connector
2024-06-29 [Hw] Decent current sense layout
2024-06-29 [Hw] Cleaning up 5V section
2024-06-29 [Hw] Tiny eeprom, all components fit on board!
2024-06-29 [Hw] Simplifying CAN
2024-06-29 [Hw] User button, tag connect placement, eeprom placement
2024-06-29 [Hw] USBC fixes, 3 wire can, encoder and comms headers
2024-06-29 [Hw] Small ICs to make 3 wire can possible in this formfactor
2024-06-29 [Hw] Untangled isolation jumpers
2024-06-29 [Hw] All connections completed - only DRC left
2024-06-29 [Hw] Routing topology complete
2024-06-29 [Hw] Aligned DRV IC, thick power traces
2024-06-29 [Hw] Optimised pin out for routing, new layout
2024-06-29 [Hw] Added labels to silkscreen
2024-06-29 [Hw] Optimised components for JLC basic parts
2024-06-29 [Hw] Version 0.1.0 - sent for manufacture
2024-06-29 [docs] Updating readme
2024-06-29 [docs] Finished initial hardware testing
2024-06-30 [Hw] WIP begun revisions for v0.2.0
2024-07-01 [Hw] Unpinched Vcc to 3.4mm width
2024-07-05 [Hw] Plane geometry changes, more legible silkscreen
2025-10-20 [Hw] Using advanced timer for PWM generation, and general purpose for encoder input
2025-10-21 [Hw] LCSC versions of isolated CAN parts
2025-10-21 [Hw] Rerouted for timer swap, usb replaced, hall pullups topside, silk version
2025-10-23 XT30(2+2)PB-M.G.B
2025-10-23 [Hw] Connector adaptor for motor integration
2025-10-24 [Hw] Rough adaptor board layout, and form factor
2025-10-26 Adaptor boards
    - CAN/Power XT30 2+2
    - Break out Aux ports to 10 and 8 pin jst GH
    - AS5046D encoder board with 10 pin jst GH connector
2025-10-27 [Hw] Cleaned up schematic, 10m isense shunts, green power led, DRC
2025-10-27 [Hw] Finished adaptor board, passes DRC
2025-11-06 [Hw] Cleaning up for V1.0
2025-11-06 [Hw] Version 1.0 manufacturing files
2025-11-06 [Hw] Adaptor board 1.0 manufacturing files
2025-11-06 Don't ignore .csv manufacturing files
2025-11-06 [Hw] Do not exclude isolation components from BOM
2025-11-06 [Hw] Use a LED that matches the footrpint
